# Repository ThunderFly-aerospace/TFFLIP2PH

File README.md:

# TFFLIP2PH - Flipper Zero to Pixhawk peripheral adapter

TFFLIP2PH is a compact hardware adapter that allows [Flipper Zero](https://flipper.net) to interface with peripherals using the Pixhawk / Dronecode connector standard. The board exposes common Pixhawk-style peripheral interfaces (UART, I2C, SPI, PWM) and provides regulated 5 V peripheral power, enabling rapid sensor prototyping, testing, and demonstration directly from Flipper Zero. This project is intended as a development and experimental tool, not as a flight controller or flight-qualified hardware.

## Features

* Flipper Zero GPIO to Pixhawk-compatible JST-GH connectors
* Supported interfaces:

  * UART (peripheral devices, telemetry, modems)
  * I2C (sensors)
  * SPI (high-speed sensors)
  * PWM (RC servos, basic actuator testing)
* 5 V peripheral power supply (from Flipper Zero)
* Compact form factor suitable for flat sensors mounting on the back of Flipper Zero
* Designed as a [Small external module](https://docs.flipper.net/zero/development/hardware/modules-blueprints#NIlXe) for Flipper Zero

## Typical use cases

* Rapid prototyping of sensors with Flipper Zero
* Bringing up new hardware using UART / I2C / SPI
* Laboratory testing and output control
* Educational and demonstration purposes
* Basic [servo testing via PWM](https://github.com/ThunderFly-aerospace/flipper-servotester)
* Internal testing and QA tooling

## Construction notes

* Peripheral connectors follow Pixhawk (Dronecode) standard pinouts**
* Peripheral power output: 5 V @ 1A
* Power is sourced from the Flipper Zero switching power supply
* Users are responsible for verifying:

  * Maximal current consumption
  * voltage compatibility
  * signal level requirements of connected devices

⚠️ **Do not connect this board to a powered Pixhawk autopilot or other flight hardware.**

## Mechanical concept

The board is designed to be mounted flat at the top of Flipper Zero, with connectors oriented parallel to the PCB surface. This allows attached peripherals to be mechanically fixed using tape or hook-and-loop fasteners on the back of the flipper zero for portable experimentation.

PCB is designed in the way that only one side is populated by JST connectors. Therefore, there exist two variants for use.

### "Flight controller" mode

In this configuration, the Flipper acts as a "Flight Controller" and connected devices are peripherals. 

### TF Payload mode

This use case sets Flipper as a "Payload device". The Flipper is therefore connected between [TFGPS](https://docs.thunderfly.cz/avionics/TFGPS01/) and a flight controller.

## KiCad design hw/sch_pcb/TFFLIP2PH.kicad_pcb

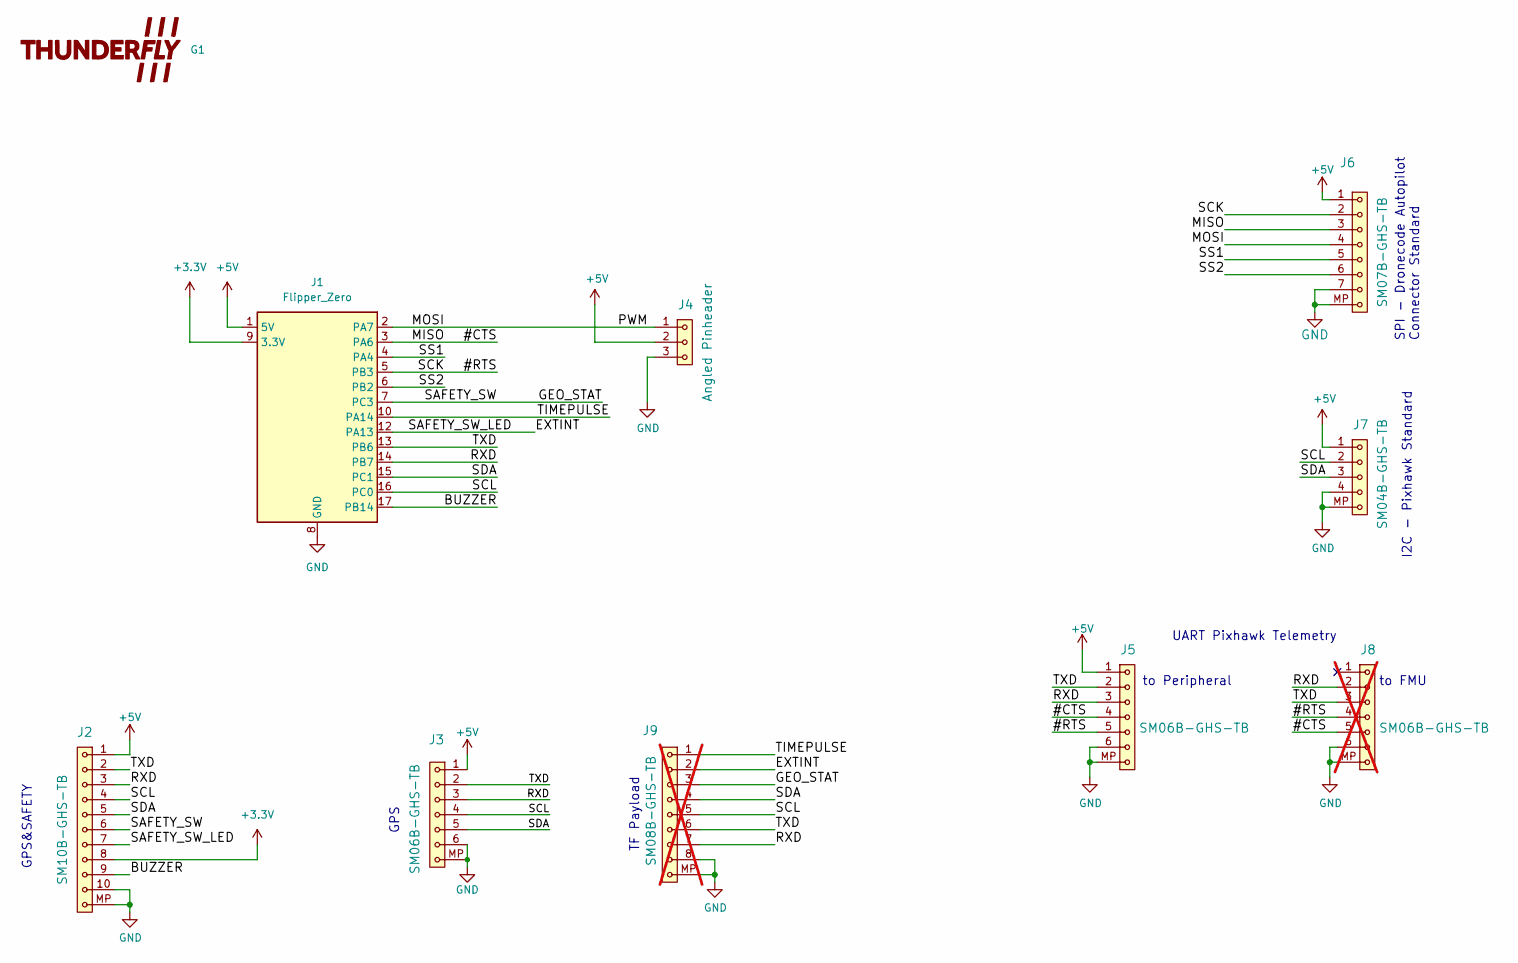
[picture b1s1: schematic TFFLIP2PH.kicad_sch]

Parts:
G1: LOGO; TF 10x4,7
J1: Flipper_Zero; Flipper_Zero_Straight
J2: SM10B-GHS-TB; JST_GH_SM10B-GHS-TB_1x10-1MP_P1.25mm_Horizontal
J3, J5: SM06B-GHS-TB; JST_GH_SM06B-GHS-TB_1x06-1MP_P1.25mm_Horizontal
J4: Angled Pinheader; PinHeader_1x03_P2.54mm_Horizontal
J6: SM07B-GHS-TB; JST_GH_SM07B-GHS-TB_1x07-1MP_P1.25mm_Horizontal
J7: SM04B-GHS-TB; JST_GH_SM04B-GHS-TB_1x04-1MP_P1.25mm_Horizontal
J8: SM06B-GHS-TB; JST_GH_SM06B-GHS-TB_1x06-1MP_P1.25mm_Horizontal; not fitted
J9: SM08B-GHS-TB; JST_GH_SM08B-GHS-TB_1x08-1MP_P1.25mm_Horizontal; not fitted

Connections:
+3.3V: J1.9 (3.3V), J2.8
+5V: J1.1 (5V), J2.1, J3.1, J4.2, J5.1, J6.1, J7.1
/#CTS: J1.3 (PA6), J5.4, J6.3, J8.5
/#RTS: J1.5 (PB3), J5.5, J6.2, J8.4
/BUZZER: J1.17 (PB14), J2.9
/EXTINT: J1.12 (PA13), J2.7, J9.2
/GEO_STAT: J1.7 (PC3), J2.6, J9.3
/MOSI: J1.2 (PA7), J4.1, J6.4
/RXD: J1.14 (PB7), J2.3, J3.3, J5.3, J8.2, J9.7
/SCL: J1.16 (PC0), J2.4, J3.4, J7.2, J9.5
/SDA: J1.15 (PC1), J2.5, J3.5, J7.3, J9.4
/SS1: J1.4 (PA4), J6.5
/SS2: J1.6 (PB2), J6.6
/TIMEPULSE: J1.10 (PA14), J9.1
/TXD: J1.13 (PB6), J2.2, J3.2, J5.2, J8.3, J9.6
GND: J1.8 (GND), J1.11 (GND), J1.18 (GND), J2.10, J2.MP, J3.6, J3.MP, J4.3, J5.6, J5.MP, J6.7, J6.MP, J7.4, J7.MP, J8.6, J8.MP, J9.8, J9.MP

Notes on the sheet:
GPS
UART Pixhawk Telemetry
to FMU
SPI - Dronecode Autopilot Connector Standard
I2C - Pixhawk Standard
TF Payload
to Peripheral
GPS&SAFETY

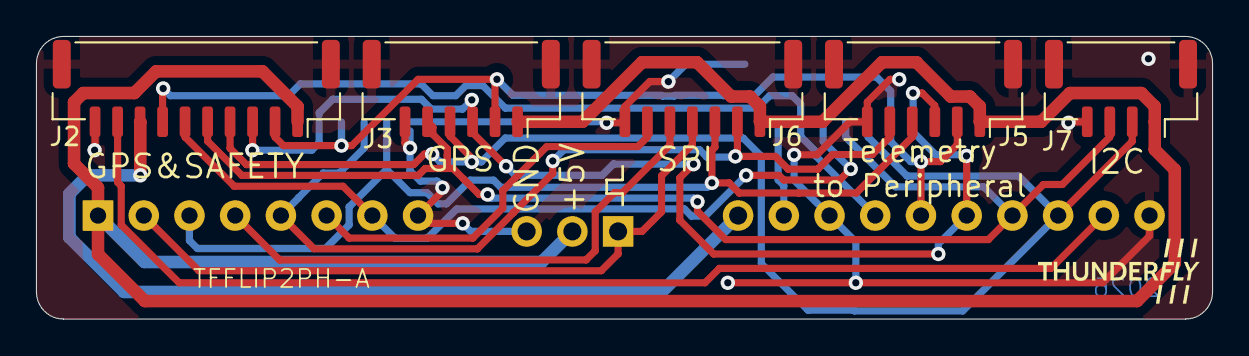
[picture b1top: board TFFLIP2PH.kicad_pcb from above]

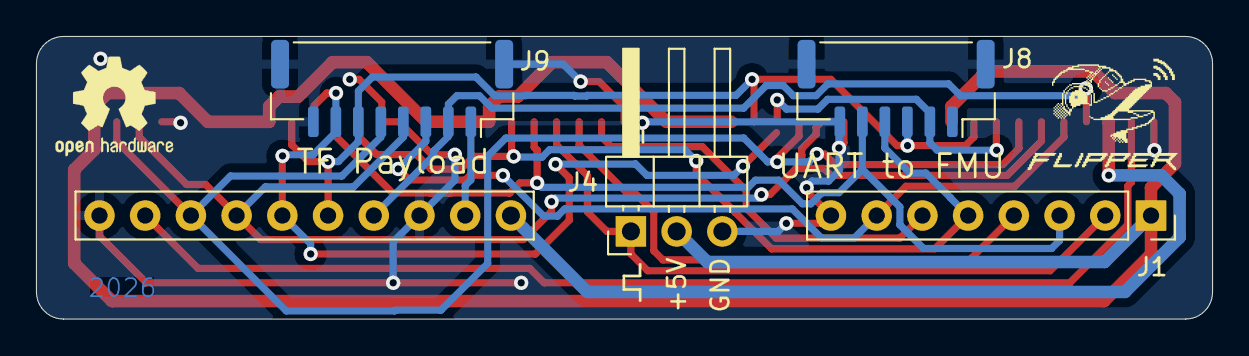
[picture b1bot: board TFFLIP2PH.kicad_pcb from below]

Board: 2 copper layers, 65.3 x 15.7 mm, 10 parts (4 on the bottom side), 16 nets.

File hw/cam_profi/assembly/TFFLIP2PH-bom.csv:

Component,Description,Part,References,Value,Footprint,Quantity Per PCB,Datasheet,ust_id
1,1x03 2.54 mm pitch header,HEADER_1x03,J4,Angled Pinheader,PinHeader_1x03_P2.54mm_Horizontal,1,5c70984412875079b91f879d,
2,Flipper Zero is a portable multi-tool for pentesters and geeks in a toy-like body,Flipper_Zero,J1,Flipper_Zero,Flipper_Zero_Straight,1,https://docs.flipper.net/development,
3,,SM04B-GHS-TB,J7,SM04B-GHS-TB,JST_GH_SM04B-GHS-TB_1x04-1MP_P1.25mm_Horizontal,1,,5c86273d1287500b4e0280be
4,1x07 2.54 mm pitch header,SM06B-GHS-TB,J3J5,SM06B-GHS-TB,JST_GH_SM06B-GHS-TB_1x06-1MP_P1.25mm_Horizontal,2,,5fa0f70212875025b3977932
5,1x08 2.54 mm pitch header,SM07B-GHS-TB,J6,SM07B-GHS-TB,JST_GH_SM07B-GHS-TB_1x07-1MP_P1.25mm_Horizontal,1,,5c7250081287500b4e112e78
6,1x08 2.54 mm pitch header,SM08B-GHS-TB,J9,SM08B-GHS-TB,JST_GH_SM08B-GHS-TB_1x08-1MP_P1.25mm_Horizontal,1,,5fa0f75012875025b3977948
7,"Zásuvka; kabel-pl.spoj; vidlice; GH; 1,25mm; PIN: 10; SMT; 50V; 1A",SM10B-GHS-TB,J2,SM10B-GHS-TB,JST_GH_SM10B-GHS-TB_1x10-1MP_P1.25mm_Horizontal,1,,5fa0f69e12875025b397791d

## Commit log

2026-01-02 Initial template of Flipper Zero small module.
2026-01-02 Update workflow files
2026-01-02 Fix KiCAD project name.
2026-01-02 Update actions products
2026-01-02 Swap board sides to match top view on flipper zero.
2026-01-02 Fix pin-header orientation.
2026-01-02 Update README.md
    Add PCB images.
2026-01-02 Restore accidentally deleted OSHW logo.
2026-01-03 Initial set of connectors.
2026-01-05 Routing in progress.
2026-01-07 Fully routed PCB.
2026-01-07 Fix DRC errors.
2026-01-07 Improve layout and silkscreen.
2026-01-29 Fixed #1
2026-01-29 Update silkscreen and manufacturing attributes.
2026-02-15 Automatic update of KiCAD outputs
2026-03-28 Update assets submodule.
2026-03-29 Change KiBot source to MLAB fork with bottom side mirror fix.
